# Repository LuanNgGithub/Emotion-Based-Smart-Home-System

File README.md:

# Emotion-Adaptive Smart Home
Repository for Emotion-Adaptive Smart Home

[Project management (Team 06)](https://pushgd10re5p.larksuite.com/base/LZFZbZlYla9m4zsmLQGupiIKs9e?table=tbl0MZkUSxeu3IoC&view=vewp7nmiS4)

Check out our Wiki for our latest update!
[Wiki](https://github.com/LuanNgGithub/Emotion-Based-Smart-Home-System/wiki)

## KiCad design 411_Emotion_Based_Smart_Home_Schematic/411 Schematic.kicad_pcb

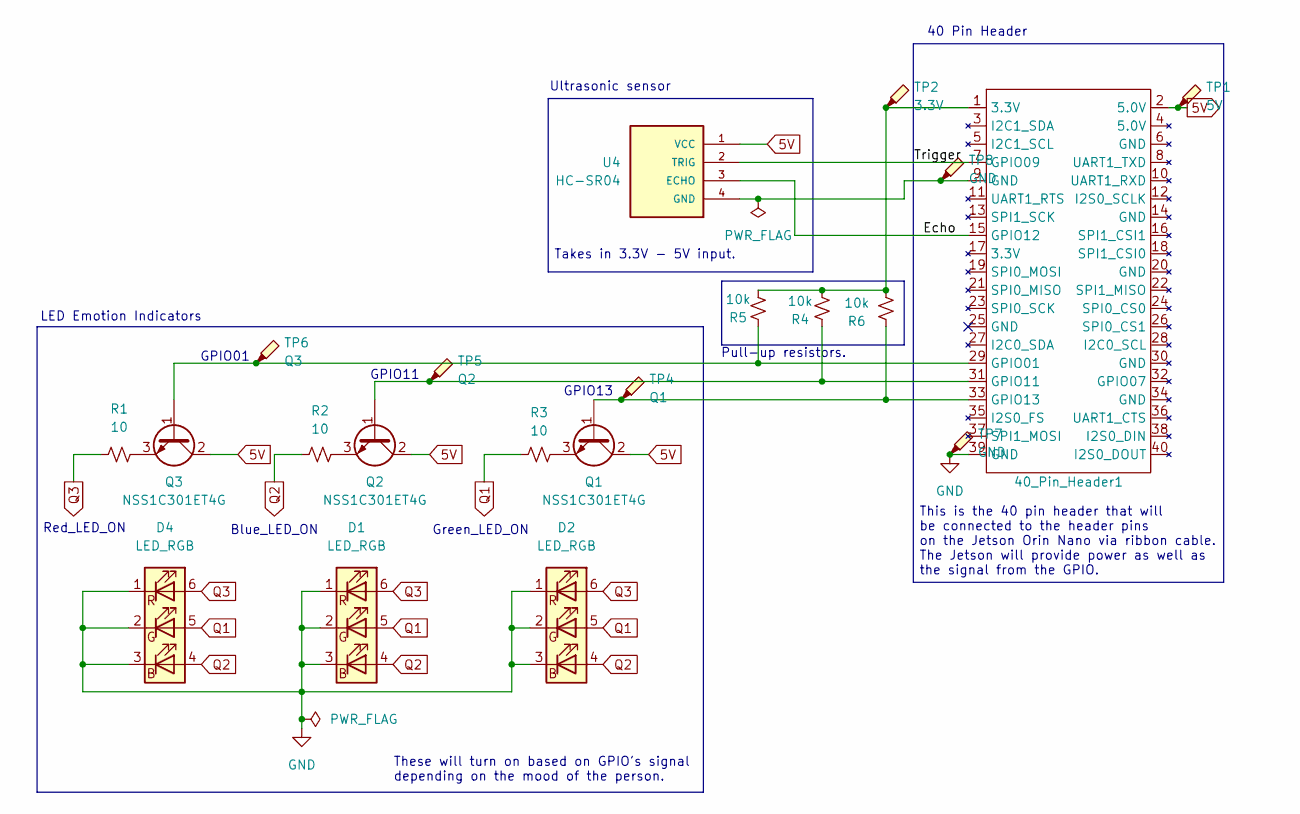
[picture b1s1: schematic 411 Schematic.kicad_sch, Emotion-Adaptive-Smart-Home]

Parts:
40_Pin_Header1: PinHeader_2x40_P2.54mm_Vertical
D1, D2, D4: LED_RGB; LED_RGB_5050-6
Q1, Q2, Q3: NSS1C301ET4G; DPAK-4_6P22X6P73_ONS
R1, R2, R3: 10; R_Axial_DIN0411_L9.9mm_D3.6mm_P5.08mm_Vertical
R4, R5, R6: 10k; R_Axial_DIN0411_L9.9mm_D3.6mm_P5.08mm_Vertical
TP1: 5V; TestPoint_Pad_1.0x1.0mm
TP2: 3.3V; TestPoint_Pad_1.0x1.0mm
TP4: Q1; TestPoint_Pad_1.0x1.0mm
TP5: Q2; TestPoint_Pad_1.0x1.0mm
TP6: Q3; TestPoint_Pad_1.0x1.0mm
TP7, TP8: GND; TestPoint_Pad_1.0x1.0mm
U4: HC-SR04; PinSocket_1x04_P2.54mm_Vertical

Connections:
5V: 40_Pin_Header1.2 (5.0V), Q1.2 (C), Q2.2 (C), Q3.2 (C), TP1.1, U4.1 (VCC)
/Echo: 40_Pin_Header1.15 (GPIO12), U4.3 (ECHO)
/Trigger: 40_Pin_Header1.7 (GPIO09), U4.2 (TRIG)
GND: 40_Pin_Header1.39 (GND), D1.1 (RK), D1.2 (GK), D1.3 (BK), D2.1 (RK), D2.2 (GK), D2.3 (BK), D4.1 (RK), D4.2 (GK), D4.3 (BK), TP7.1
unnamed: 40_Pin_Header1.1 (3.3V), R4.1, R5.1, R6.1, TP2.1
unnamed: 40_Pin_Header1.29 (GPIO01), Q3.1 (B), R5.2, TP6.1
unnamed: 40_Pin_Header1.31 (GPIO11), Q2.1 (B), R4.2, TP5.1
unnamed: 40_Pin_Header1.33 (GPIO13), Q1.1 (B), R6.2, TP4.1
unnamed: Q1.3 (E), R3.2
unnamed: Q2.3 (E), R2.2
unnamed: Q3.3 (E), R1.2
unnamed: 40_Pin_Header1.9 (GND), TP8.1, U4.4 (GND)
Q1: D1.5 (GA), D2.5 (GA), D4.5 (GA), R3.1
Q2: D1.4 (BA), D2.4 (BA), D4.4 (BA), R2.1
Q3: D1.6 (RA), D2.6 (RA), D4.6 (RA), R1.1

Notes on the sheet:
Pull-up resistors.
GPIO11
GPIO13
This is the 40 pin header that will be connected to the header pins on the Jetson Orin Nano via ribbon cable. The Jetson will provide power as well as the signal from the GPIO.
Takes in 3.3V - 5V input.
Blue_LED_ON
LED Emotion Indicators
Ultrasonic sensor
These will turn on based on GPIO's signal depending on the mood of the person.
Green_LED_ON
Red_LED_ON
GPIO01
40 Pin Header

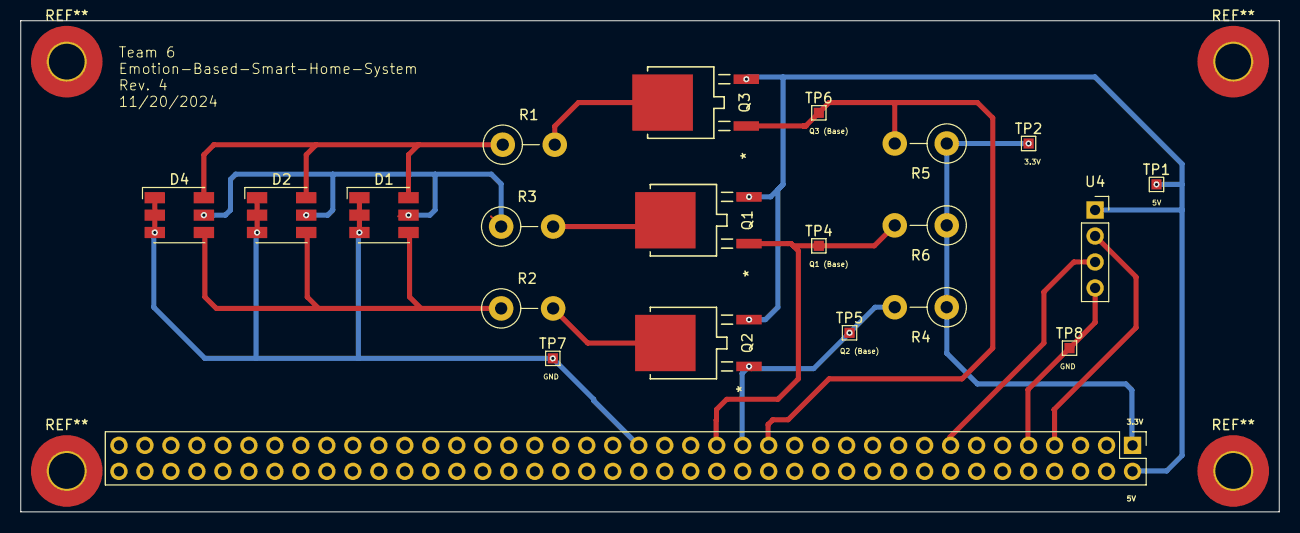
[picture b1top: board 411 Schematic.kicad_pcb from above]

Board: 2 copper layers, 123.0 x 48.0 mm, 21 parts (0 on the bottom side), 15 nets.

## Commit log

2024-10-24 Initial coding testing
2024-10-24 Coding
2024-10-24 Weights
2024-10-31 Create Ultrasonic Sensor
2024-10-31 Create LICENSE
2024-11-02 Update README.md
    Changing name to match our documents
2024-11-03 Add files via upload
    update the code
2024-11-07 Current updated schematic
2024-11-07 Current Schematic
    This is the schematic that Luan and Kamal are actively working on
2024-11-07 Updated Kicad design
    This is our updated kicad, we still need to add the speaker and finish the camera
2024-11-07 Updated again
    Fixed an error and made the GND on the USB camera passive
2024-11-07 Entire design folder
    We had to move this into it's own seperate file to get the PCB design to work. Will fix names later
2024-11-07 Updating our Schematic and Layout
    Altering things in the schematic and layout before we turn this in
2024-11-07 report
2024-11-07 Update README.md
    Added wiki page link
2024-11-07 Update README.md
    Fixing The Wiki Link
2024-11-07 Delete 411_Emotion_Based_Smart_Home_Schematic/~411 Schematic.kicad_sch.lck
    Removing the Lock file
2024-11-07 Delete 411_Emotion_Based_Smart_Home_Schematic/~411 Schematic.kicad_pcb.lck
    Removing this lock file
2024-11-09 Added folder for ultrasonic sensor.
2024-11-09 Added a comment.
2024-11-09 Organized folders.
2024-11-12 Added spec sheet for LED and BJT.
2024-11-13 Added folder for BOM and Footprint.
2024-11-13 Updating schematic
    Testing if this works
2024-11-13 Removed the pdf and added screenshot of the receipt.
2024-11-13 Added LED RGB footprint
2024-11-13 Added Level 0 & Level 1 Block Diagram.drawio
2024-11-14 5050 LED Schematic.drawio
2024-11-14 5050 LED and Transistor Schematic.drawio
2024-11-14 Updating what I have of schematic
2024-11-14 Updated the schematic.
2024-11-14 Fixing Errors
2024-11-14 No Errors!
    This PCB currently has no error in ERC
2024-11-14 PCB Rough route and schematic almost finished
2024-11-14 Modified size of PCB frame
2024-11-14 Removing .lck files agian
2024-11-17 Updated schematic.
2024-11-19 Added TP and cleaned up all the traces.
2024-11-21 Updated schematic and layout.
2024-12-12 Updated schematic.
    Added limiting resistors to each GPIO pins.
2024-12-12 Updated schematic again. Should work now.
2024-12-12 main code
2024-12-13 Updated schematic.
    Changed from Pin 15 to Pin 32.
